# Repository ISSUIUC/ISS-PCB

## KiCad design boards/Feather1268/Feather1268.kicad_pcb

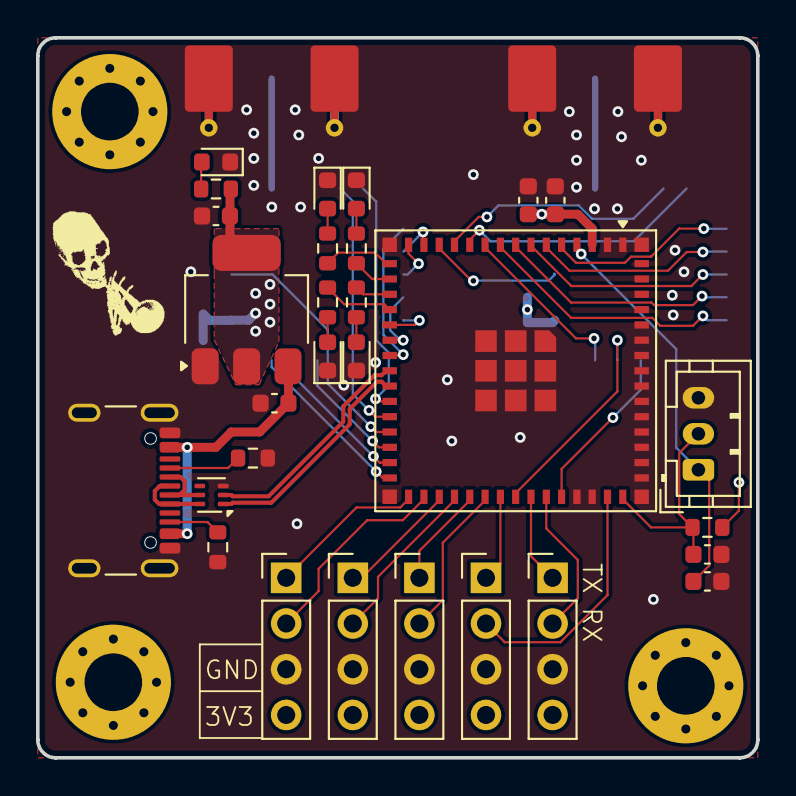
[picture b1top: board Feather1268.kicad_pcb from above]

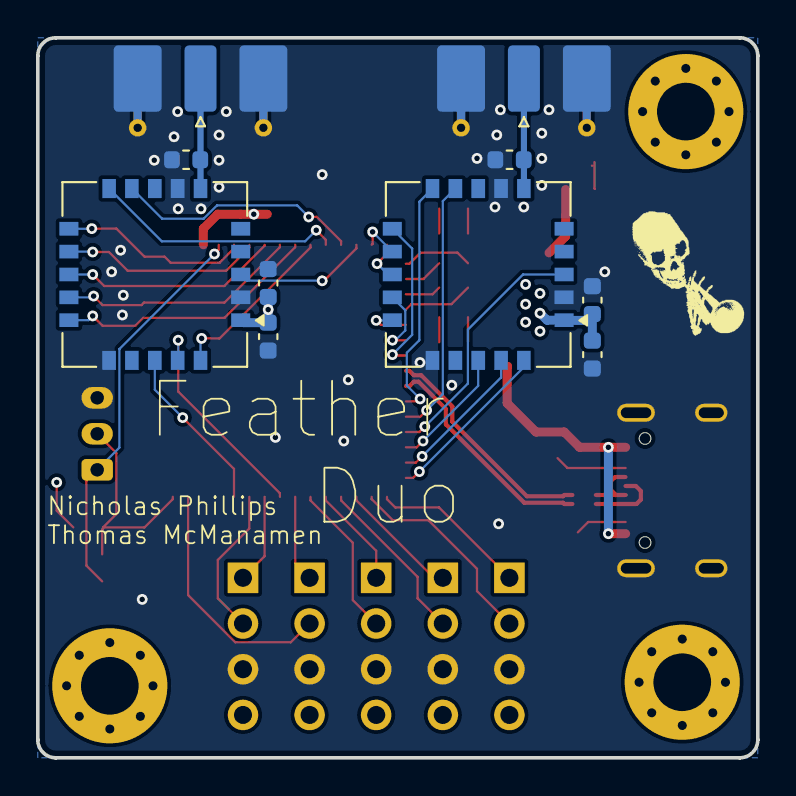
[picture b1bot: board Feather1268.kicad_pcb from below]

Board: 4 copper layers, 40.0 x 40.0 mm, 42 parts (10 on the bottom side), 54 nets.

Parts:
C101, C106: 22uF; C_0603_1608Metric
C102: 0.1uF; C_0603_1608Metric
C103, C104: 1uF; C_0603_1608Metric
C105, C201, C301: 10uF; C_0603_1608Metric
C202, C302: 10nF; C_0603_1608Metric
D101, D105: RED LED; LED_0603_1608Metric
D102: ORANGE LED; LED_0603_1608Metric
D103: GREEN LED; LED_0603_1608Metric
D104: BLUE LED; LED_0603_1608Metric
H101, H102, H103: M3; MountingHole_3.2mm_M3_Pad_Via
J101, J102, J104, J105, J107: Conn_01x04; PinHeader_1x04_P2.54mm_Vertical
J103: Conn_01x03; JST_PH_B3B-PH-K_1x03_P2.00mm_Vertical
J106: USB4105-GF-A; USB_C_Receptacle_GCT_USB4105-xx-A_16P_TopMnt_Horizontal
J201, J301: SMA; SMA_Molex_73251-2120_EdgeMount_Horizontal
L201, L301: 330nH; L_0603_1608Metric
R101: 20k; R_0603_1608Metric
R102, R103, R104, R105, R108: 1k; R_0603_1608Metric
R106, R107: 5.1k; R_0603_1608Metric
U101: ESP32-S3-MINI-1U; ESP32-S2-MINI-1U
U102: ECMF02-2AMX6; ST_UQFN-6L_1.5x1.7mm_P0.5mm
U103: AMS1117-3.3; SOT-223-3_TabPin2
U201, U301: E22-400MM22S

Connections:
+3V3: C101.2, C102.2, C106.1, C201.1, C202.1, C301.1, C302.1, J101.4, J102.4, J104.4, J105.4, J107.4, R101.1, R108.1, U101.3 (3V3), U103.2 (VO), U201.1 (VCC), U301.1 (VCC)
+5V: C105.1, J106.A4 (VBUS), J106.A9 (VBUS), J106.B4 (VBUS), J106.B9 (VBUS), U103.3 (VI)
/BOOT: C104.1, J103.1, U101.4 (IO0)
/D+: J106.A6 (D+), J106.B6 (D+), U102.6 (D+_out)
/D-: J106.A7 (D-), J106.B7 (D-), U102.5 (D-_out)
/E22_BUSY_0: U101.5 (IO1), U201.11 (BUSY)
/E22_BUSY_1: U101.22 (IO18), U301.11 (BUSY)
/E22_CS_0: U101.8 (IO4), U201.14 (NSS)
/E22_CS_1: U101.21 (IO17), U301.14 (NSS)
/E22_DI01_0: U101.10 (IO6), U201.20 (DIO1)
/E22_DI01_1: U101.30 (IO48), U301.20 (DIO1)
/E22_DI02_0: U101.38 (IO42), U201.19 (DIO2)
/E22_DI02_1: U101.29 (IO34), U301.19 (DIO2)
/E22_DI03_0: U101.41 (IO45), U201.18 (DIO3)
/E22_DI03_1: U101.28 (IO33), U301.18 (DIO3)
/E22_RESET_0: U101.13 (IO9), U201.3 (NRST)
/E22_RESET_1: U101.27 (IO47), U301.3 (NRST)
/E22_RXEN_0: U101.11 (IO7), U201.10 (RXEN)
/E22_RXEN_1: U101.25 (IO21), U301.10 (RXEN)
/E22_TXEN_0: U101.12 (IO8), U201.9 (TXEN)
/E22_TXEN_1: U101.26 (IO26), U301.9 (TXEN)
/IO35: J101.1, U101.31 (IO35)
/IO36: J101.2, U101.32 (IO36)
/IO37: J102.1, U101.33 (IO37)
/IO38: J102.2, U101.34 (IO38)
/IO39: J104.1, U101.35 (IO39)
/IO40: J104.2, U101.36 (IO40)
/IO41: J105.1, U101.37 (IO41)
/IO46: J105.2, U101.44 (IO46)
/LED_BLUE: R105.1, U101.19 (IO15)
/LED_GREEN: R104.1, U101.18 (IO14)
/LED_ORANGE: R103.1, U101.17 (IO13)
/LED_RED: R102.1, U101.16 (IO12)
/RESET: C103.1, J103.2, R101.2, U101.45 (EN)
/RX: J107.2, U101.40 (RXD0)
/SPI_MISO_0: U101.6 (IO2), U201.12 (MISO)
/SPI_MISO_1: U101.14 (IO10), U301.12 (MISO)
/SPI_MOSI_0: U101.7 (IO3), U201.13 (MOSI)
/SPI_MOSI_1: U101.15 (IO11), U301.13 (MOSI)
/SPI_SCK_0: U101.9 (IO5), U201.15 (SCK)
/SPI_SCK_1: U101.20 (IO16), U301.15 (SCK)
/TX: J107.1, U101.39 (TXD0)
/USB_D+: U101.24 (IO20), U102.1 (D+_in)
/USB_D-: U101.23 (IO19), U102.2 (D-_in)
GND: C101.1, C102.1, C103.2, C104.2, C105.2, C106.2, C201.2, C202.2, C301.2, C302.2, D101.1 (K), D102.1 (K), D103.1 (K), D104.1 (K), D105.1 (K), J101.3, J102.3, J103.3, J104.3, J105.3, J106.A1 (GND), J106.A12 (GND), J106.B1 (GND), J106.B12 (GND), J106.S1 (SHIELD), J107.3, J201.2 (Ext), J301.2 (Ext), L201.2, L301.2, R106.2, R107.2, U101.1 (GND), U101.2 (GND), U101.42 (GND), U101.43 (GND), U101.46 (GND), U101.47 (GND), U101.48 (GND), U101.49 (GND), U101.50 (GND), U101.51 (GND), U101.52 (GND), U101.53 (GND), U101.54 (GND), U101.55 (GND), U101.56 (GND), U101.57 (GND), U101.58 (GND), U101.59 (GND), U101.60 (GND), U101.61 (GND), U101.62 (GND), U101.63 (GND), U101.64 (GND), U101.65 (GND), U102.3 (GND), U103.1 (GND), U201.2 (GND), U201.7 (GND), U201.16 (GND), U301.2 (GND), U301.7 (GND), U301.16 (GND)
unnamed: D101.2 (A), R102.2
unnamed: D102.2 (A), R103.2
unnamed: D103.2 (A), R104.2
unnamed: D104.2 (A), R105.2
unnamed: D105.2 (A), R108.2
unnamed: J106.A5 (CC1), R106.1
unnamed: J106.B5 (CC2), R107.1
unnamed: J201.1 (In), L201.1, U201.6 (ANT)
unnamed: J301.1 (In), L301.1, U301.6 (ANT)

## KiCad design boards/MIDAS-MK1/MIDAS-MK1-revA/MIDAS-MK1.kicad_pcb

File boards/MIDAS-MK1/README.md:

# MIDAS MK1

MIDAS MK1 is the fifth generation of the Illinois Space Society's SRAD avionics systems and the first to serve as a full-fledged rocketry altimeter. Combining the functionality of TARS together with the advanced pyrotechnic circuitry seen on many commercial models into a smaller form factor, MIDAS facilitates data collection, telemetry, and execution of inflight events. More than just a single unit, MIDAS is intended for placement on multiple stages of a rocket and can serve as a center of more complex avionics networks such as our onboard live video system.

Three MIDAS boards have been produced, flying over forty-four thousand feet to a new UIUC altitude record on Kairos II. By providing continuous telemetry that allowed for successful retrieval of both stages, MIDAS proved itself as a critical part of the team's avionics ecosystem going forward.

Future iterations of MIDAS will optimize operation and reliability at exceedingly high ranges and altitudes, creating a space-capable altimeter that will take our team to the Kármán line.

Read more about MIDAS and the surrounding avionics systems in the [MIDAS MK1 Report](https://uofi.box.com/s/6l9kr9wvrg0xpj17jzni7ou9mbe10vdm).

# Schematics

Printable PDF schematics for MIDAS MK1.1 revA can be found in the PDFs folder.

# Renders

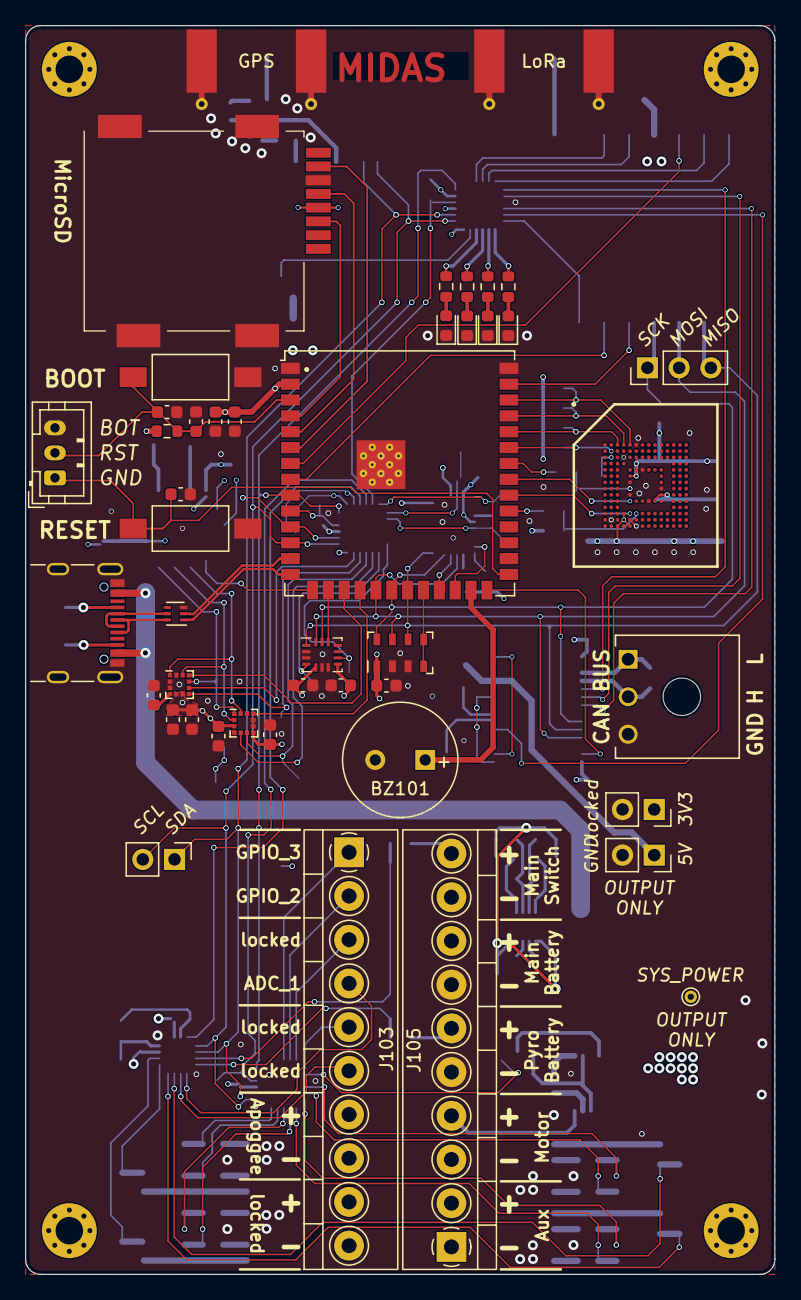
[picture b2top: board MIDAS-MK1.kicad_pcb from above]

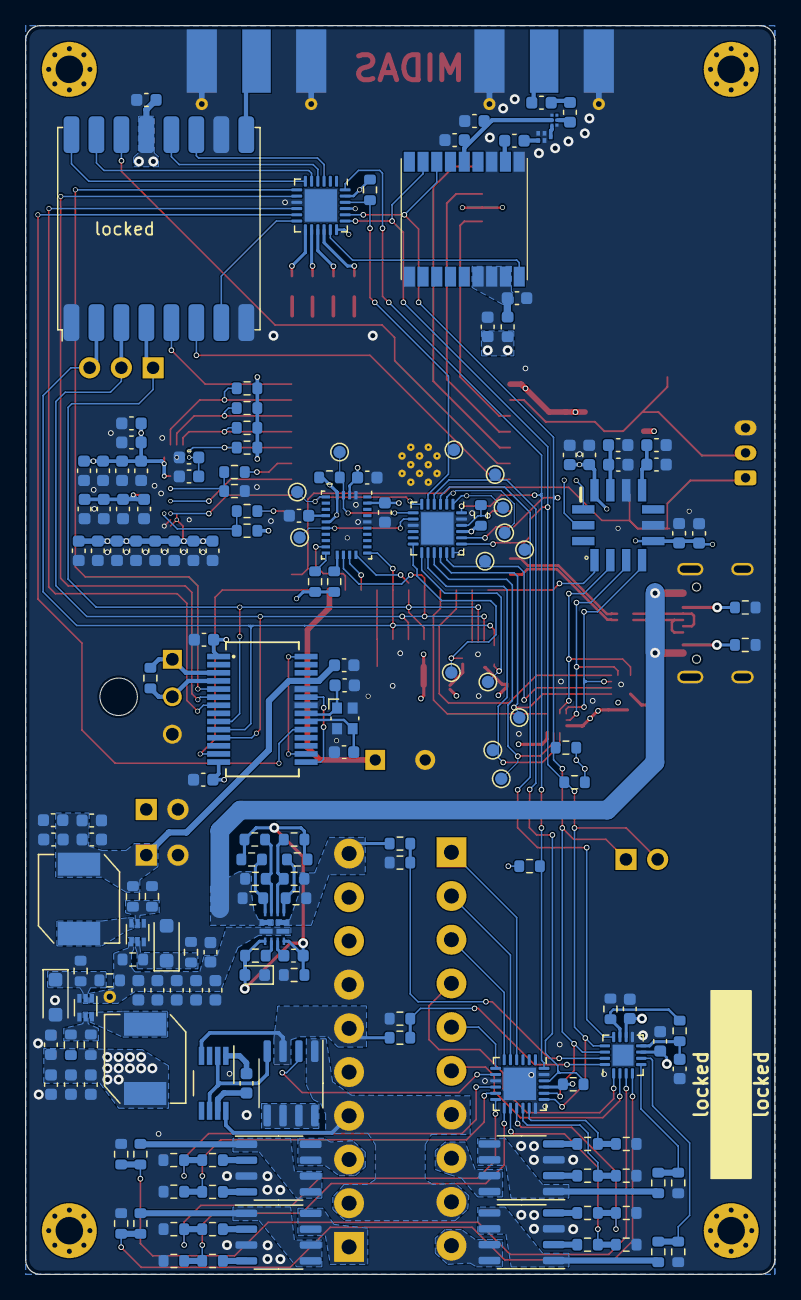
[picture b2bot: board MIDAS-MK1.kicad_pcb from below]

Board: 4 copper layers, 60.0 x 100.0 mm, 221 parts (174 on the bottom side), 159 nets.

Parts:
BZ101: AT-0927-TT-6-R; Buzzer_AT-0927-TT-6-R
C101, C102, C104, C105, C109, C112, C114, C117, C119, C121, C123, C125, C127, C129, C131, C133, C302, C303, C502, C504, C506, C507, C508, C510, C511, C512, C513, C514, C515, C519: 0.1uF; C_0603_1608Metric
C103, C108, C110, C111, C115, C201, C301, C501, C503, C505, C509, C516: 1uF; C_0603_1608Metric
C106, C107: 18pF; C_0603_1608Metric
C113, C308, C309, C310, C311, C312, C313, C314, C315: 22uF; C_0603_1608Metric
C116, C118, C120, C122, C124, C126, C128, C130, C132: 2.2uF; C_0603_1608Metric
C304, C305, C306, C307, C402: 10uF; C_0603_1608Metric
C401: 140pF; C_0603_1608Metric
C403: 1nF; C_0603_1608Metric
C404: 120pF; C_0603_1608Metric
C405, C406, C407: 56pF; C_0603_1608Metric
C517, C518: 100nF; C_0603_1608Metric
D101: RED LED; LED_0603_1608Metric
D102: ORANGE LED; LED_0603_1608Metric
D103: GREEN LED; LED_0603_1608Metric
D104: BLUE LED; LED_0603_1608Metric
D301: D; D_0603_1608Metric
D302, D303: BZT52H-A5V1-QX; D_SOD-123F
FL401: B4327; SMD-5
H101, H102, H103, H104: M2; MountingHole_2.2mm_M2_Pad_Via
J101, J102: Conn_01x02; PinSocket_1x02_P2.54mm_Vertical
J103: Left; Molex_Terminal-Block_393570010_1x10_P3.5mm
J104: JST_PH_B3B-PH-K_1x03_P2.00mm_Vertical
J105: Right; Molex_Terminal-Block_393570010_1x10_P3.5mm
J106: USB4105-GF-A; USB_C_Receptacle_GCT_USB4105-xx-A_16P_TopMnt_Horizontal
J107: 2157601003; Molex_Micro-Fit-Plus_2157601003_1x03_P3.0mm
J108: PJS008-4100-0-VE
J109: Conn_01x02; PinHeader_1x02_P2.54mm_Vertical
J110: PinHeader_1x03_P2.54mm_Vertical
J301: TestPoint; TestPoint_THTPad_D1.0mm_Drill0.5mm
J401, J402: SMA; SMA_Molex_732511153_EdgeMount_Horizontal
L301, L302: 2.2uH; L_TDK_SPM6530
L401: 5.6nH; L_0603_1608Metric
L402: 27nH; L_0603_1608Metric
Q201, Q202, Q203, Q204, Q205: DMNH6022SSDQ; SO-8_3.9x4.9mm_P1.27mm
R101, R102, R103, R104, R105, R106, R122, R123, R209, R210, R221, R222, R501: 10k; R_0603_1608Metric
R107, R118, R120: 100k; R_0603_1608Metric
R108: TBD; R_0603_1608Metric
R109, R110, R111, R114, R115: 50k; R_0603_1608Metric
R112, R113: 22; R_0603_1608Metric
R116: 50; R_0603_1608Metric
R117: 120; R_0603_1608Metric
R119, R121, R318: 220k; R_0603_1608Metric
R124, R125, R126, R127: 470; R_0603_1608Metric
R128: 10K; R_0603_1608Metric
R201, R202, R203, R204, R213, R214, R215, R216: 3.3k; R_0603_1608Metric
R205, R206, R207, R208, R217, R218, R219, R220: 1k; R_0603_1608Metric
R211, R212, R223, R224: 22k; R_0603_1608Metric
R301: 7.3k; R_0603_1608Metric
R302, R304, R306, R308: 5k; R_0603_1608Metric
R303: 23.3k; R_0603_1608Metric
R305: 44k; R_0603_1608Metric
R307: 65k; R_0603_1608Metric
R309: 0; R_0603_1608Metric
R310: 18.7k; R_0603_1608Metric
R311, R312: 20k; R_0603_1608Metric
R313, R314, R315, R316: 30k; R_0603_1608Metric
R317: 135k; R_0603_1608Metric
R502, R503: 2.2k; R_0603_1608Metric
SW101, SW102: SW_Push; SW_SPST_FSMSM
TP101, TP102, TP103, TP104, TP105, TP106, TP107, TP108, TP109, TP110, TP111, TP112, TP113, TP114: TestPoint_Small; TestPoint_Pad_D1.0mm
U101, U102, U103: TCAL9539-Q1; WQFN-24-1EP_4x4mm_P0.5mm_EP2.6x2.6mm
U104: MCP251863; SSOP-28
U105: ADS7138-Q1; WQFN-16-1EP_3x3mm_P0.5mm_EP1.68x1.68mm
U106: MTFCxxxx; TFBGA-153_11.5x13mm
U107: ESP32-S3-WROOM-1U
U108: ECMF02-2AMX6; ST_UQFN-6L_1.5x1.7mm_P0.5mm
U201: LM74670-Q1; VSSOP-8_3.0x3.0mm_P0.65mm
U301: TPS2121; VQFN-HR-RUX0012A
U302, U303: TI_TPS566242DRLR; SOT-563
U401: RFM96W-433S2; HOPERF_RFM9XW_SMD
U402: BGA725L6; TSNP-6-2
U403: Teseo-LIV3R
U501: KX134-1211; LGA-12_2x2mm_P0.5mm
U502: ADXL355; Analog_LGA_14-7.4x7.4mm
U503: LSM6DSLTR; Bosch_LGA-14_3x2.5mm_P0.5mm
U504: BNO086; LGA-28_5.2x3.8mm_P0.5mm
U505: LIS3MDL; LGA-12_2x2mm_P0.5mm
U506: MS5611-01BA03; LGA-8_3x5mm_P1.25mm
Y101: 40MHz; Crystal_SMD_Abracon_ABM10-4Pin_2.5x2.0mm

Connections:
+3V3: C101.2, C102.2, C108.1, C110.1, C113.1, C114.1, C116.1, C117.1, C118.1, C119.1, C120.1, C121.1, C122.1, C123.1, C124.1, C125.1, C126.1, C127.1, C128.1, C129.1, C130.1, C131.1, C132.1, C133.1, C308.1, C310.1, C312.1, C314.1, C402.1, C407.1, C501.2, C502.2, C503.2, C504.1, C506.1, C508.1, C511.1, C512.1, C514.1, C515.1, C516.2, C517.2, C519.1, J101.1, J108.4 (VDD), L301.1, L402.1, R101.2, R102.2, R103.2, R104.2, R105.2, R106.2, R109.2, R110.2, R111.2, R114.2, R115.2, R128.2, R317.2, R501.2, R502.2, R503.2, U101.21 (VCC), U102.18 (A0), U102.21 (VCC), U103.18 (A0), U103.21 (VCC), U103.23 (A1), U104.1 (VIO), U104.14 (VDD), U105.7 (AVDD), U105.10 (DVDD), U106.C6 (VCCQ), U106.E6 (VCC), U106.F5 (VCC), U106.J10 (VCC), U106.K9 (VCC), U106.M4 (VCCQ), U106.N4 (VCCQ), U106.P3 (VCCQ), U106.P5 (VCCQ), U107.2 (3V3), U401.13 (3.3V), U501.3 (VDDIO), U501.7 (VDD), U502.5 (VDDIO), U502.11 (VSUPPLY), U503.5 (VDDIO), U503.8 (VDD), U504.3 (VDD), U504.5 (PS1), U504.10 (CLKSEL0), U504.28 (VDDIO), U505.5 (VDD), U505.6 (VDD_IO), U506.1 (VDD)
+5V: C105.2, C309.1, C311.1, C313.1, C315.1, J102.1, L302.1, R318.2, U104.25 (VCC)
/ADC_ALERT: TP103.1, U102.3 (P02), U105.12 (ALERT)
/ADC_DECAP: C103.1, R107.1, U105.8 (DECAP)
/ADXL355_CS: U107.15 (IO3), U502.1 (~CS/SCL)
/ADXL355_INT1: TP108.1, U102.1 (P00), U502.13 (INT2)
/ADXL355_INT2: TP107.1, U102.2 (P01), U502.12 (INT1)
/ARM_A: R201.1, R205.1, U101.16
/ARM_B: R213.1, R217.1, U101.14
/ARM_C: R202.1, R207.1, U101.10
/ARM_D: R214.1, R219.1, U101.12
/AUX_ADC_0: J103.6, U105.2 (AIN3/GPIO3)
/AUX_ADC_1: J103.4, U105.1 (ANI2/GPIO2)
/AUX_GPIO_0: J103.5, U101.7 (P06)
/AUX_GPIO_1: J103.3, U101.6 (P05)
/AUX_GPIO_2: J103.2, U101.5 (P04)
/AUX_GPIO_3: J103.1, U101.4 (P03)
/BNO086_BOOT: R501.1, TP106.1, U102.7 (P06), U504.4 (BOOTN)
/BNO086_CS: U107.23 (IO21), U504.18 (H_CSN)
/BNO086_INT: U107.24 (IO47), U504.14 (H_INTN)
/BNO086_RESET: TP104.1, U102.8 (P07), U504.11 (NRST)
/BNO086_WAKE: TP105.1, U102.6 (P05), U504.6 (PS0/WAKE)
/BOOT_SW: C104.2, J104.1, SW101.2, U107.27 (IO0)
/BUZZER: BZ101.1 (-), U107.25 (IO48)
/CAN_CANH: J107.1, R117.1, U104.3 (CANL)
/CAN_CANL: J107.2, R117.2, U104.4 (CANH)
/CAN_NCS: U104.13 (NCS), U107.26 (IO45)
/CAN_NINT: U103.11, U104.19 (NINT)
/CAN_NINT0: U103.10, U104.7 (NINT0/GPIO0/XSTBY)
/CAN_NINT1: U103.8 (P07), U104.6 (NINT1/GPIO1)
/CAN_STBY: U103.7 (P06), U104.5 (STBY)
/EXP_INT0: R101.1, TP101.1, U101.22 (~INT), U102.4 (P03)
/EXP_INT1: R102.1, U102.22 (~INT), U107.10 (IO17)
/EXP_INT2: R103.1, TP102.1, U102.5 (P04), U103.22 (~INT)
/EXP_RESET: R106.1, U101.24 (~RESET), U102.24 (~RESET), U103.24 (~RESET), U107.9 (IO16)
/FIRE_A: R203.1, R206.1, U101.17
/FIRE_B: R215.1, R218.1, U101.15
/FIRE_C: R204.1, R208.1, U101.11
/FIRE_D: R216.1, R220.1, U101.13
/I2C_SCL: J109.2, R105.1, U101.19 (SCL), U102.19 (SCL), U103.19 (SCL), U105.13 (SCL), U107.12 (IO8), U403.17 (SCL)
/I2C_SDA: J109.1, R104.1, U101.20 (SDA), U102.20 (SDA), U103.20 (SDA), U105.14 (SDA), U107.11 (IO18), U403.16 (SDA)
/KX134_CS: U107.18 (IO10), U501.10 (nCS)
/KX134_INT1: TP110.1, U102.14, U501.5 (INT1)
/KX134_INT2: TP109.1, U102.15, U501.6 (INT2)
/LED_BLUE: R127.1, U103.13
/LED_GREEN: R126.1, U103.14
/LED_ORANGE: R125.1, U103.15
/LED_RED: R124.1, U103.16
/LIS3MDL_CS: U107.17 (IO9), U505.10 (CS)
/LIS3MDL_DRDY: TP111.1, U102.17, U505.8 (DRDY)
/LIS3MDL_INT: TP112.1, U102.16, U505.7 (INT)
/LIV3F_RESET: U103.17, U403.9 (SYS_RSTN)
/LSM6DSLTR_INT1: TP113.1, U102.13, U503.4 (INT1)
/LSM6DSLTR_INT2: TP114.1, U102.12, U503.9 (INT2)
/LSM6DSL_CS: U107.16 (IO46), U503.12 (CS)
/MEM_CLK: R112.1, U107.31 (IO38)
/MEM_CMD: U106.M5 (CMD), U107.32 (IO39)
/MEM_DAT0: R114.1, U106.A3 (DAT0), U107.36 (RXD0)
/MEM_DAT1: R111.1, U106.A4 (DAT1), U107.37 (TXD0)
/MEM_DAT2: R110.1, U106.A5 (DAT2), U107.38 (IO2)
/MEM_DAT3: R109.1, U106.B2 (DAT3), U107.35 (IO42)
/MEM_DS: R113.2, U107.34 (IO41)
/MEM_RST_N: U106.K5 (RST_N), U107.33 (IO40)
/MS5611_CS: U107.22 (IO14), U506.4 (CSB), U506.5 (CSB)
/MicroSD_CLK: J108.5 (CLK), U107.5 (IO5)
/MicroSD_CMD: J108.3 (CMD), U107.4 (IO4)
/MicroSD_DAT0: J108.7 (DAT0), U107.6 (IO6)
/PYRO_A: J103.8, Q202.7 (D1), Q202.8 (D1)
/PYRO_B: J103.10, Q204.7 (D1), Q204.8 (D1)
/PYRO_C: J105.3, Q203.7 (D1), Q203.8 (D1)
/PYRO_D: J105.1, Q205.7 (D1), Q205.8 (D1)
/PYRO_EN: Q201.2 (G1), U101.8 (P07)
/PYRO_SENSE: R118.2, R119.1, U105.16 (AIN1/GPIO1)
/Power/SYS_POWER: C302.1, C303.1, C304.1, C305.1, C306.1, C307.1, J301.1, R311.1, R312.1, U301.1 (OUT), U301.8 (OUT), U302.1 (VIN), U303.1 (VIN)
/RESET_SW: C109.1, C115.1, J104.2, R128.1, SW102.1, U107.3 (EN)
/RF/VCC_RF: C403.2, C405.1, U402.2 (VCC), U403.14 (VCC_RF)
/RFM96W_CS: U107.39 (IO1), U401.5 (NSS)
/RFM96W_DI01: U103.5 (P04), U401.15 (DIO1)
/RFM96W_DI02: U103.6 (P05), U401.16 (DIO2)
/RFM96W_DI03: U103.3 (P02), U401.11 (DIO3)
/RFM96W_DI04: U103.4 (P03), U401.12 (DIO4)
/RFM96W_DI05: U103.12, U401.7 (DIO5)
/RFM96W_INT: U107.8 (IO15), U401.6 (RESET)
/RFM96W_RESET: U107.7 (IO7), U401.14 (DIO0)
/SENSE_A: R210.1, R211.2, U105.5 (AIN6/GPIO6)
/SENSE_B: R221.1, R223.2, U105.6 (AIN7/GPIO7)
/SENSE_C: R209.1, R212.2, U105.3 (AIN4/GPIO4)
/SENSE_D: R222.1, R224.2, U105.4 (AIN5/GPIO5)
/SPI_MISO: J110.3, U104.10 (SDI), U107.21 (IO13), U401.2 (MISO), U501.1 (SDO/ADDR), U502.4 (MISO/ASEL), U503.1 (SDO/SA0), U504.20 (H_SDA/H_MISO/TX), U505.9 (SDO/SA1), U506.6 (SDO)
/SPI_MOSI: J110.2, U104.11 (SDO), U107.19 (IO11), U401.3 (MOSI), U501.2 (SDI/SDA), U502.3 (MOSI/SDA), U503.14 (SDA), U504.17 (H_SA0_MOSI), U505.11 (SDA/SDI/SDO), U506.7 (SDI/SDA)
/SPI_SCK: J110.1, U104.9 (SCK), U107.20 (IO12), U401.4 (SCK), U501.12 (SCLK/SCL), U502.2 (SCLK/VSSIO), U503.13 (SCL), U504.19 (H_SCL/SCK/RX), U505.1 (SCL/SPC), U506.8 (SCLK)
/USB_D+: U107.14 (IO20), U108.1 (D+_in)
/USB_D-: U107.13 (IO19), U108.2 (D-_in)
/USB_POWER: J106.A4 (VBUS), J106.A9 (VBUS), J106.B4 (VBUS), J106.B9 (VBUS), R301.1, R303.1, U301.7 (IN1)
/VBAT: J105.10, R120.1, R305.1, R307.1, U301.2 (IN2)
/VBAT_PYRO: J105.6, Q201.3 (S2), R118.1, U201.4 (ANODE)
/VBAT_SENSE: R120.2, R121.1, U105.15 (AIN0/GPIO0)
/V_PYRO: J103.7, J103.9, J105.2, J105.4, Q201.1 (S1), U201.8 (CATHODE)
GND: BZ101.2 (+), C101.1, C102.1, C103.2, C104.1, C105.1, C106.1, C107.2, C108.2, C109.2, C110.2, C111.1, C112.1, C113.2, C114.2, C115.2, C116.2, C117.2, C118.2, C119.2, C120.2, C121.2, C122.2, C123.2, C124.2, C125.2, C126.2, C127.2, C128.2, C129.2, C130.2, C131.2, C132.2, C133.2, C302.2, C303.2, C304.2, C305.2, C306.2, C307.2, C308.2, C309.2, C310.2, C311.2, C312.2, C313.2, C314.2, C315.2, C402.2, C403.1, C405.2, C406.2, C407.2, C501.1, C502.1, C503.1, C504.2, C505.1, C506.2, C507.2, C508.2, C509.1, C510.2, C511.2, C512.2, C513.2, C514.2, C515.2, C516.1, C517.1, C518.1, C519.2, D101.1 (K), D102.1 (K), D103.1 (K), D104.1 (K), D301.1 (K), D302.2 (A), D303.2 (A), FL401.2 (GND), FL401.3 (GND), FL401.5 (GND), J101.2, J102.2, J104.3, J105.5, J105.7, J106.A1 (GND), J106.A12 (GND), J106.B1 (GND), J106.B12 (GND), J106.S1 (SHIELD), J107.3, J108.6 (VSS), J108.9 (SHIELD), J401.2 (Ext), J402.2 (Ext), Q202.3 (S2), Q203.3 (S2), Q204.3 (S2), Q205.3 (S2), R108.2, R116.2, R119.2, R121.2, R122.2, R123.2, R201.2, R202.2, R203.2, R204.2, R211.1, R212.1, R213.2, R214.2, R215.2, R216.2, R223.1, R224.1, R309.2, R313.2, R314.2, R315.2, R316.2, SW101.1, SW102.2, U101.9 (GND), U101.18 (A0), U101.23 (A1), U101.25 (GND), U102.9 (GND), U102.23 (A1), U102.25 (GND), U103.9 (GND), U103.25 (GND), U104.22 (VSS), U104.24 (GND), U105.9 (GND), U105.17 (EPAD), U106.A6 (VSS), U106.C4 (VSSQ), U106.E7 (VSS), U106.G5 (VSS), U106.H10 (VSS), U106.J5 (VSS), U106.K8 (VSS), U106.N2 (VSSQ), U106.N5 (VSSQ), U106.P4 (VSSQ), U106.P6 (VSSQ), U107.1 (GND), U107.40 (GND), U107.41 (EPAD), U108.3 (GND), U302.3 (GND), U302.4 (AGND), U303.3 (GND), U303.4 (AGND), U401.1 (GND), U401.8 (GND), U401.10 (GND), U402.1 (GND), U402.4 (GNDRF), U403.1 (GND), U403.10 (GND_RF), U403.12 (GND_RF), U501.4 (TRIG), U501.8 (GND), U501.9 (GND), U502.6 (VSSIO), U502.9 (VSS), U503.2 (SDX), U503.3 (SCX), U503.6 (GND), U503.7 (GND), U504.2 (GND), U504.25 (GNDIO), U505.2 (GND), U505.3 (GND), U505.12 (GND), U506.2 (PS), U506.3 (GND), Y101.2, Y101.4
unnamed: C401.2, L401.1
unnamed: D101.2 (A), R124.2
unnamed: D102.2 (A), R125.2
unnamed: D103.2 (A), R126.2
unnamed: D104.2 (A), R127.2
unnamed: C301.1, D301.2 (A), R302.2, R304.2, R306.2, R308.2, R309.1, R310.1, U301.9 (ST), U301.12 (GND)
unnamed: D302.1 (K), R311.2, R313.1, U302.2 (EN)
unnamed: D303.1 (K), R312.2, R314.1, U303.2 (EN)
unnamed: FL401.1 (IN), U402.3 (AO)
unnamed: C404.1, FL401.4 (OUT)
unnamed: J105.8, J105.9
unnamed: J106.A5 (CC1), R122.1
unnamed: J106.B5 (CC2), R123.1
unnamed: C401.1, J401.1 (In)
unnamed: J402.1 (In), U401.9 (ANT)
unnamed: Q201.5 (D2), Q201.6 (D2), Q201.7 (D1), Q201.8 (D1)
unnamed: Q201.4 (G2), U201.2 (GATE_PULL_DOWN), U201.6 (GATE_DRIVE)
unnamed: Q202.2 (G1), R205.2
unnamed: Q202.1 (S1), Q202.5 (D2), Q202.6 (D2), R210.2
unnamed: Q202.4 (G2), R206.2
unnamed: Q203.2 (G1), R207.2
unnamed: Q203.1 (S1), Q203.5 (D2), Q203.6 (D2), R209.2
unnamed: Q203.4 (G2), R208.2
unnamed: Q204.2 (G1), R217.2
unnamed: Q204.1 (S1), Q204.5 (D2), Q204.6 (D2), R221.2
unnamed: Q204.4 (G2), R218.2
unnamed: Q205.2 (G1), R219.2
unnamed: Q205.1 (S1), Q205.5 (D2), Q205.6 (D2), R222.2
unnamed: Q205.4 (G2), R220.2
unnamed: C107.1, U104.21 (OSC1), Y101.1
unnamed: C106.2, U104.20 (OSC2), Y101.3
unnamed: U104.16 (RXCAN), U104.28 (RXD)
unnamed: U104.15 (TXCAN), U104.23 (TXD)
unnamed: R107.2, R108.1, U105.11 (ADDR)
unnamed: R112.2, R115.1, U106.M6 (CLK)
unnamed: R113.1, R116.1, U106.H5 (DS)
unnamed: C111.2, C112.2, U106.C2 (VDDIM)
unnamed: J106.A6 (D+), J106.B6 (D+), U108.6 (D+_out)
unnamed: J106.A7 (D-), J106.B7 (D-), U108.5 (D-_out)
unnamed: C201.1, U201.7 (VCAPH)
unnamed: C201.2, U201.1 (VCAPL)
unnamed: R305.2, R306.1, U301.3 (CP2)
unnamed: R310.2, U301.10 (ILM)
unnamed: R303.2, R304.1, U301.5 (OV1)
unnamed: R307.2, R308.1, U301.4 (OV2)
unnamed: R301.2, R302.1, U301.6 (PR1)
unnamed: C301.2, U301.11 (SS)
unnamed: R315.1, R317.1, U302.5 (FB)
unnamed: L301.2, U302.6 (SW)
unnamed: R316.1, R318.1, U303.5 (FB)
unnamed: L302.2, U303.6 (SW)
unnamed: L401.2, U402.5 (AI)
unnamed: C404.2, U403.11 (RF_IN)
unnamed: C406.1, L402.2, U403.6 (VBATT), U403.7 (VCC_IO), U403.8 (VCC)
unnamed: C505.2, C507.1, U502.10 (V1P8ANA)
unnamed: C509.2, C510.1, U502.8 (V1P8DIG)
unnamed: C513.1, U504.9 (CAP)
unnamed: R503.1, U504.15 (ENV_SCL)
unnamed: R502.1, U504.16 (ENV_SDA)
unnamed: C518.2, U505.4 (C1)
